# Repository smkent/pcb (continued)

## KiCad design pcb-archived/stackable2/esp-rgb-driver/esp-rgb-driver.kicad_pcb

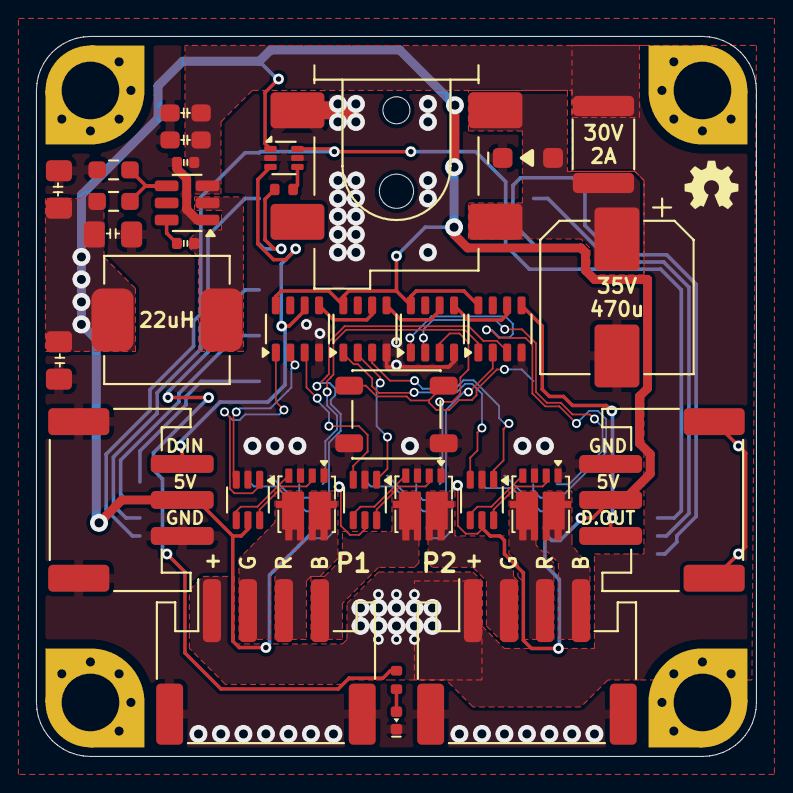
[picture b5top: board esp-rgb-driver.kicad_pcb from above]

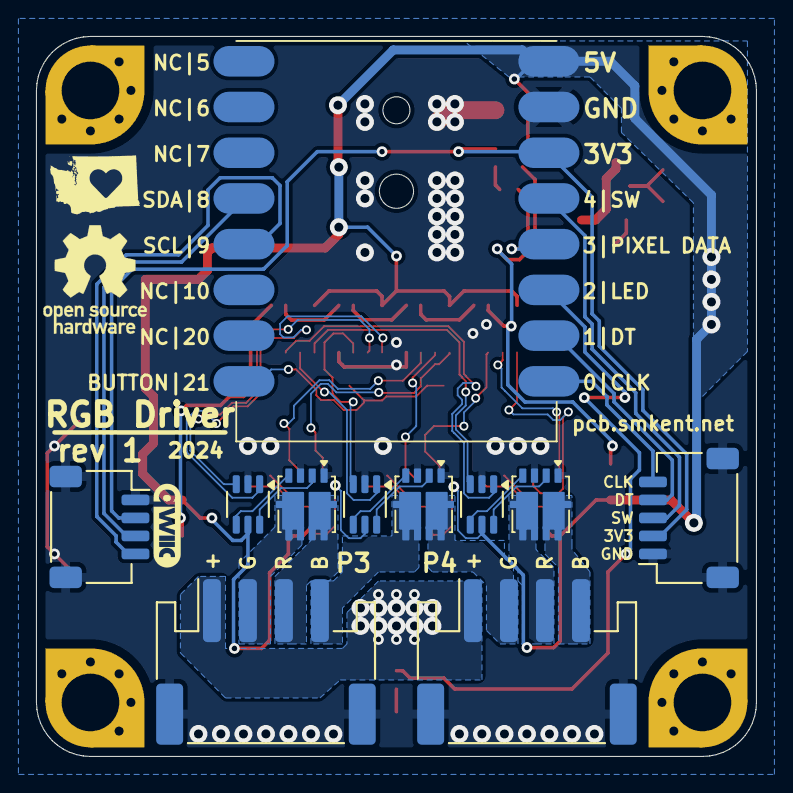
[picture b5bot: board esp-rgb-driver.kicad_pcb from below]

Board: 2 copper layers, 40.0 x 40.0 mm, 45 parts (11 on the bottom side), 59 nets.

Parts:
C0: 470u; CP_Elec_8x10
C1, C2: 10u; C_0603_1608Metric_Pad1.08x0.95mm_HandSolder
C3, C4: 0u1; C_0402_1005Metric
C5, C6, C7: 22u; C_0805_2012Metric_Pad1.18x1.45mm_HandSolder
D1: D_TVS; D_SOD-123F
F1: 30V 2A; Fuse_1812_4532Metric
J0: Barrel Jack; BarrelJack_DC-050_SMT_Horizontal
J1, J2, J3, J4: JST PH; JST_PH_S4B-PH-SM4-TB_1x04-1MP_P2.00mm_Horizontal
J5, J6: STEMMA-Signal; STEMMA-Signal-SMD-horizontal
J7: JST SH; JST_SH_SM05B-SRSS-TB_1x05-1MP_P1.00mm_Horizontal
J8: Qwiic; Qwiic-SMD-horizontal-logo
L1: 22u; L_Power_7.0x6.6mm_0630
LED1: LED; LED_0402_1005Metric
Q1, Q2, Q3, Q4, Q5, Q6: ZC010DNG; PDFN-8_L3.2-W3.1-P0.65-LS3.4-BL-EP2
R1: 100K; R_0603_1608Metric_Pad0.98x0.95mm_HandSolder
R2: 13K3; R_0603_1608Metric_Pad0.98x0.95mm_HandSolder
R3: 300R; R_0402_1005Metric
R4: 10K; R_0402_1005Metric
SM1: ESP32-C3-Super-Mini-Castellated-SMD-only
SW1: SW_Push; SW_SPST_PTS647_Sx50
U1: TPS54202DDCR; SOT-23-6
U2: SN74LVC1T45Z6; SOT-563
U3, U4, U5, U6: WS2811F; FSOP-8_3.3x1.7mm_P0.80mm
U7, U8, U9, U10, U11, U12: NC7WZ14P6X; SOT-363_SC-70-6_HandSolder

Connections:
+3V3: J7.2, J8.2 (+3V3), SM1.3V3 (+3.3V), U2.6 (VCCB)
+5V: C5.1, C6.1, C7.1, J5.2 (V+), J6.2 (V+), L1.2, R1.2, SM1.5V (+5V), U2.1 (VCCA), U3.8 (VDD), U4.8 (VDD), U5.8 (VDD), U6.8 (VDD), U7.5 (V_{CC}), U8.5 (V_{CC}), U9.5 (V_{CC}), U10.5 (V_{CC}), U11.5 (V_{CC}), U12.5 (V_{CC})
+24V: C1.1, C2.1, C3.1, F1.2, J1.1, J2.1, J3.1, J4.1, U1.3 (VIN)
/24V_RAW: C0.1, D1.2 (A2), F1.1, J0.1
/RGB1_B_GATE: Q2.4 (G), U8.4 (2Y)
/RGB1_G_GATE: Q1.4 (G), U7.4 (2Y)
/RGB1_R_GATE: Q1.2 (G), U7.6 (1Y)
/RGB2_B_GATE: Q3.2 (G), U9.6 (1Y)
/RGB2_G_GATE: Q2.2 (G), U8.6 (1Y)
/RGB2_R_GATE: Q3.4 (G), U9.4 (2Y)
/RGB3_B_GATE: Q5.4 (G), U11.4 (2Y)
/RGB3_G_GATE: Q4.4 (G), U10.4 (2Y)
/RGB3_R_GATE: Q4.2 (G), U10.6 (1Y)
/RGB4_B_GATE: Q6.2 (G), U12.6 (1Y)
/RGB4_G_GATE: Q5.2 (G), U11.6 (1Y)
/RGB4_R_GATE: Q6.4 (G), U12.4 (2Y)
/SW: C4.2, L1.1, U1.2 (SW)
BUTTON: SM1.21 (GPIO21/TX), SW1.1
ENCODER_BUTTON: J7.3, SM1.4 (SCK/ADC/GPIO4)
ENCODER_CLK: J7.5, SM1.0 (ADC/GPIO0)
ENCODER_DT: J7.4, SM1.1 (ADC/GPIO1)
FB: R1.1, R2.2, U1.4 (FB)
GND: C0.2, C1.2, C2.2, C3.2, C5.2, C6.2, C7.2, D1.1 (A1), J0.2, J1.MP (MountPin), J2.MP (MountPin), J3.MP (MountPin), J4.MP (MountPin), J5.3 (GND), J5.MP, J6.3 (GND), J6.MP, J7.1, J7.MP (MountPin), J8.1 (GND), J8.MP, LED1.1 (K), Q1.1 (S), Q1.3 (S), Q2.1 (S), Q2.3 (S), Q3.1 (S), Q3.3 (S), Q4.1 (S), Q4.3 (S), Q5.1 (S), Q5.3 (S), Q6.1 (S), Q6.3 (S), R2.1, SM1.G (GND), SW1.2, U1.1 (GND), U2.2 (GND), U2.5 (DIR), U3.4 (GND), U4.4 (GND), U5.4 (GND), U6.4 (GND), U7.2 (GND), U8.2 (GND), U9.2 (GND), U10.2 (GND), U11.2 (GND), U12.2 (GND)
unnamed: LED1.2 (A), R4.2
unnamed: C4.1, U1.6 (BOOT)
unnamed: R3.1, U2.4 (B)
unnamed: U3.5 (DO), U4.6 (DIN)
unnamed: U4.5 (DO), U5.6 (DIN)
unnamed: U5.5 (DO), U6.6 (DIN)
PIXEL_DATA_3V3: R3.2, SM1.3 (ADC/GPIO3)
PIXEL_DATA_5V: J5.1 (Sig), U2.3 (A), U3.6 (DIN)
PIXEL_DATA_OUT: J6.1 (Sig), U6.5 (DO)
RGB1_B: J1.4, Q2.6 (D)
RGB1_B_EN: U3.3 (OUTB), U8.3 (2A)
RGB1_G: J1.2, Q1.6 (D)
RGB1_G_EN: U3.2 (OUTG), U7.3 (2A)
RGB1_R: J1.3, Q1.5 (D)
RGB1_R_EN: U3.1 (OUTR), U7.1 (1A)
RGB2_B: J2.4, Q3.5 (D)
RGB2_B_EN: U4.3 (OUTB), U9.1 (1A)
RGB2_G: J2.2, Q2.5 (D)
RGB2_G_EN: U4.2 (OUTG), U8.1 (1A)
RGB2_R: J2.3, Q3.6 (D)
RGB2_R_EN: U4.1 (OUTR), U9.3 (2A)
RGB3_B: J3.4, Q5.6 (D)
RGB3_B_EN: U5.3 (OUTB), U11.3 (2A)
RGB3_G: J3.2, Q4.6 (D)
RGB3_G_EN: U5.2 (OUTG), U10.3 (2A)
RGB3_R: J3.3, Q4.5 (D)
RGB3_R_EN: U5.1 (OUTR), U10.1 (1A)
RGB4_B: J4.4, Q6.5 (D)
RGB4_B_EN: U6.3 (OUTB), U12.1 (1A)
RGB4_G: J4.2, Q5.5 (D)
RGB4_G_EN: U6.2 (OUTG), U11.1 (1A)
RGB4_R: J4.3, Q6.6 (D)
RGB4_R_EN: U6.1 (OUTR), U12.3 (2A)
SCL: J8.4 (SCL), SM1.9 (~GPIO9/SCL)
SDA: J8.3 (SDA), SM1.8 (~GPIO8/SDA)
STATUS_LED: R4.1, SM1.2 (ADC/~GPIO2)

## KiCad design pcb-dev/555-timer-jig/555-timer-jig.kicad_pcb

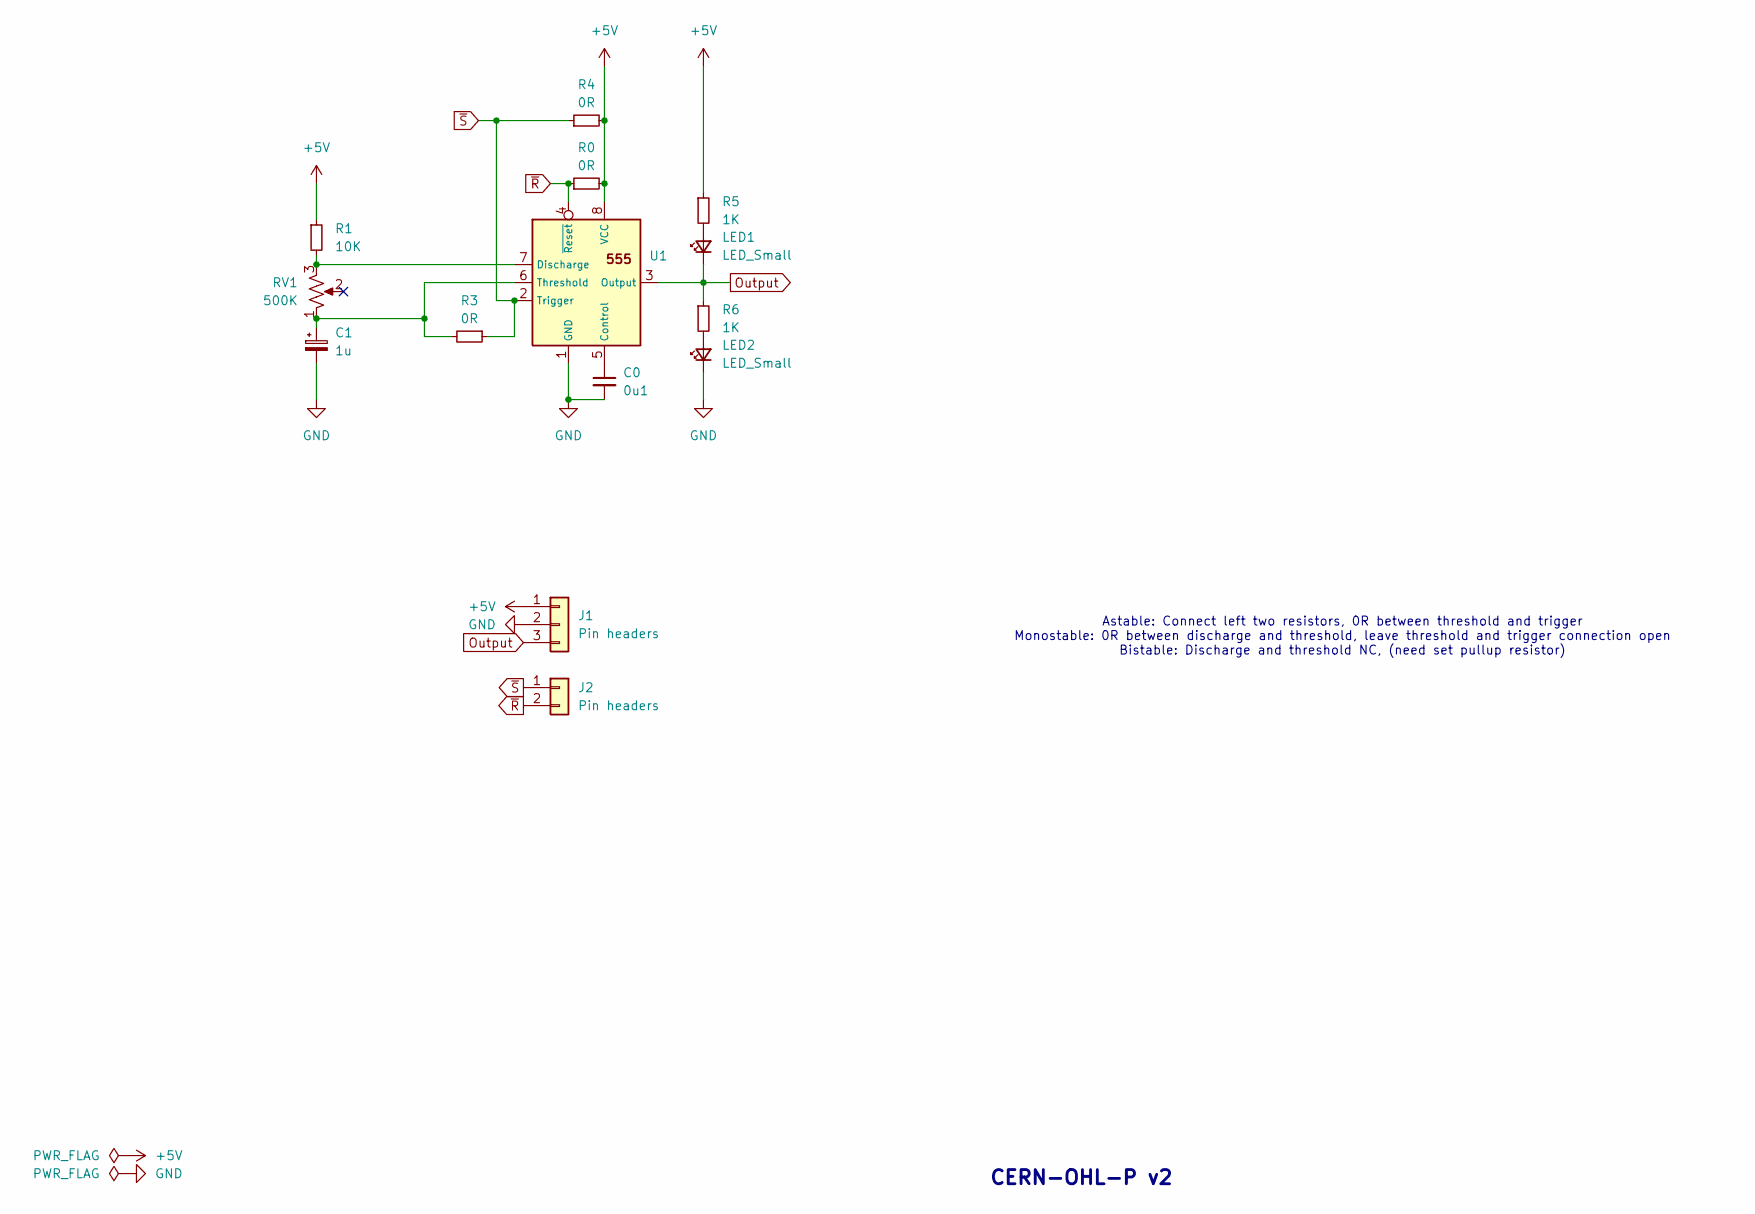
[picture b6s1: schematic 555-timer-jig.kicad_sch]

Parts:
C0: 0u1; C_0603_1608Metric_Pad1.08x0.95mm_HandSolder
C1: 1u; C_Combo_CP_Elec_5x5.4
J1: Pin headers; PinHeader_1x03_P2.54mm_Vertical_simple_pad2gnd
J2: Pin headers; PinHeader_1x02_P2.54mm_Vertical_simple
LED1, LED2: LED_Small; LED_0603_1608Metric_Pad1.05x0.95mm_HandSolder_simple
R0, R3, R4: 0R; R_0603_1608Metric_Pad0.98x0.95mm_HandSolder_simple
R1: 10K; R_0603_1608Metric_Pad0.98x0.95mm_HandSolder_simple
R5, R6: 1K; R_0603_1608Metric_Pad0.98x0.95mm_HandSolder_simple
RV1: 500K; RES-ADJ-SMD_VG039NCH
U1: NE555; SOIC-8_3.9x4.9mm_P1.27mm

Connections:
+5V: J1.1, R0.2, R1.1, R4.2, R5.1, U1.8 (VCC)
GND: C0.2, C1.2, J1.2, LED2.1 (K), U1.1 (GND)
unnamed: LED1.2 (A), R5.2
unnamed: LED2.2 (A), R6.2
unnamed: C0.1, U1.5 (Control)
unnamed: R1.2, RV1.3, U1.7 (Discharge)
unnamed: C1.1, R3.2, RV1.1, U1.6 (Threshold)
Output: J1.3, LED1.1 (K), R6.1, U1.3 (Output)
~R: J2.2, R0.1, U1.4 (~Reset)
~S: J2.1, R3.1, R4.1, U1.2 (Trigger)

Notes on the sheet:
CERN-OHL-P v2
Astable: Connect left two resistors, 0R between threshold and trigger Monostable: 0R between discharge and threshold, leave threshold and trigger connection open Bistable: Discharge and threshold NC, (need set pullup resistor)

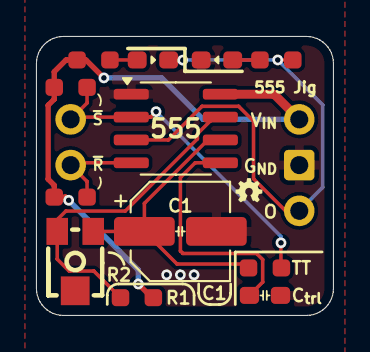
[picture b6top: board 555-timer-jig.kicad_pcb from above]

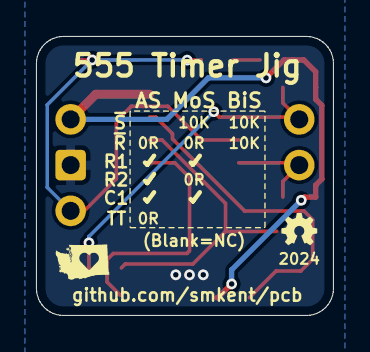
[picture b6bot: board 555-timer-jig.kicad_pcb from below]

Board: 2 copper layers, 16.5 x 15.5 mm, 14 parts (2 on the bottom side), 10 nets.

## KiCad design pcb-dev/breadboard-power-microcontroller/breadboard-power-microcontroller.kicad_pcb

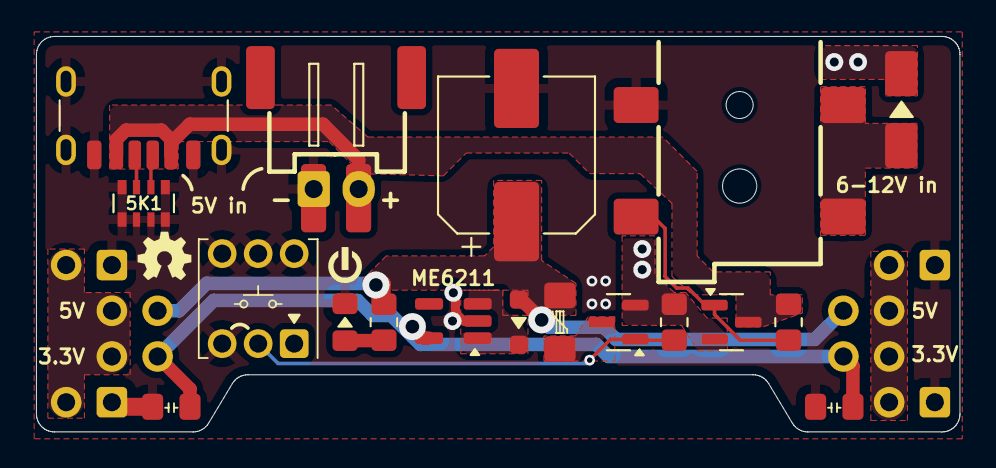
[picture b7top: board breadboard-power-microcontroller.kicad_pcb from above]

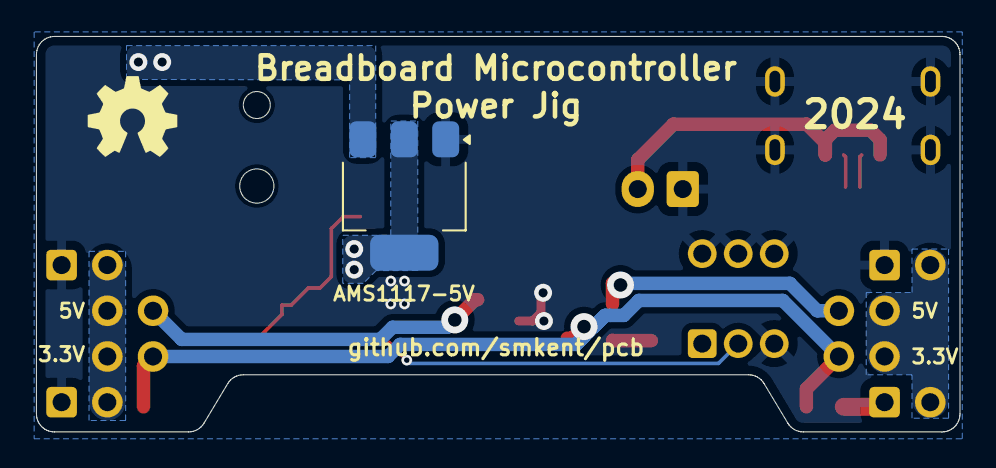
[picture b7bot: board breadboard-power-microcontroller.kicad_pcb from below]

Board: 2 copper layers, 51.3 x 22.0 mm, 25 parts (5 on the bottom side), 16 nets.

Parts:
C1: 1000uF; CP_Elec_8x10.5
C2, C3: 22uF; C_0805_2012Metric_Pad1.18x1.45mm_HandSolder
D1: SS34; D_SMA_simple
D2: BAT60A; D_SOD-323_HandSoldering_simple
D3: LED; LED_0805_2012Metric_Pad1.15x1.40mm_HandSolder_simple
F1: Polyfuse; Fuse_1206_3216Metric_Pad1.42x1.75mm_HandSolder_simple
J0: USB_C_Receptacle_PowerOnly_6P; USB_C_Receptacle_GCT_USB4125-xx-x_6P_TopMnt_Horizontal_hand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
J1: Barrel_Jack_Switch; DC-IN_DC-050-2.0-BB_rev2
J2: Conn_01x02; JST_XH_S2B-XH-2AW_1x02_P2.50mm_TH-or-SMD_pad2gnd_trim
JLEFT0, JLEFT1: Conn_01x02; PinHeader_1x02_P2.54mm_Vertical_simple_pad2gnd
JLEFT2: Conn_02x02_Counter_Clockwise; PinHeader_2x02_P2.54mm_Vertical_simple
JRIGHT0, JRIGHT1: Conn_01x02; PinHeader_1x02_P2.54mm_Vertical_simple_pad2gnd
JRIGHT2: Conn_02x02_Counter_Clockwise; PinHeader_2x02_P2.54mm_Vertical_simple
Q1, Q2: AO3401A; SOT-23
R1, R2: 10K; R_0805_2012Metric_Pad1.20x1.40mm_HandSolder
R6: 2K2; R_0805_2012Metric_Pad1.20x1.40mm_HandSolder
RN1: 5K1; R_Array_Convex_4x0603
SW1: SW_DPDT_x2; SW-TH_6P-L7.0-W7.0-P2.00_90deg
U1: AMS1117-5.0; SOT-223-3_TabPin2
U2: ME6211C33M5; SOT-23-5_HandSoldering_simple

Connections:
3V3_OUT: C2.1, C3.1, JLEFT2.4, JRIGHT2.3, U2.5 (V_{OUT})
5V_OUT: C1.1, D2.2 (A), F1.2, JLEFT2.2, JRIGHT2.1, R6.1
DC_IN_DIODE: D1.1 (K), U1.3 (VI)
DC_JACK_SWITCH: J1.3, Q2.1 (G), R1.1
GND: C1.2, C2.2, C3.2, D3.1 (K), J0.A12 (GND), J0.B12 (GND), J0.S1 (SHIELD), J1.2, J2.2, JLEFT0.2, JLEFT1.2, JRIGHT0.2, JRIGHT1.2, RN1.1 (R1.1), RN1.4 (R4.1), RN1.5 (R4.2), RN1.6 (R3.2), RN1.7 (R2.2), RN1.8 (R1.2), SW1.3 (C), SW1.4 (A), SW1.5 (B), SW1.6 (C), U1.1 (GND), U2.2 (V_{SS})
unnamed: D3.2 (A), R6.2
unnamed: J0.A5 (CC1), RN1.2 (R2.1)
unnamed: J0.B5 (CC2), RN1.3 (R3.1)
unnamed: Q1.1 (G), R2.2, SW1.2 (B)
PRE_FUSE: F1.1, Q1.3 (D)
REG_5V: Q1.2 (S), Q2.2 (S), R2.1, U1.2 (VO)
TO_3V3_DIODE: D2.1 (K), U2.1 (V_{IN}), U2.3 (CE)
VIN: J0.A9 (VBUS), J0.B9 (VBUS), J2.1, Q2.3 (D), R1.2
VIN_DC: D1.2 (A), J1.1
VOUT_LEFT: JLEFT0.1, JLEFT1.1, JLEFT2.1, JLEFT2.3
VOUT_RIGHT: JRIGHT0.1, JRIGHT1.1, JRIGHT2.2, JRIGHT2.4

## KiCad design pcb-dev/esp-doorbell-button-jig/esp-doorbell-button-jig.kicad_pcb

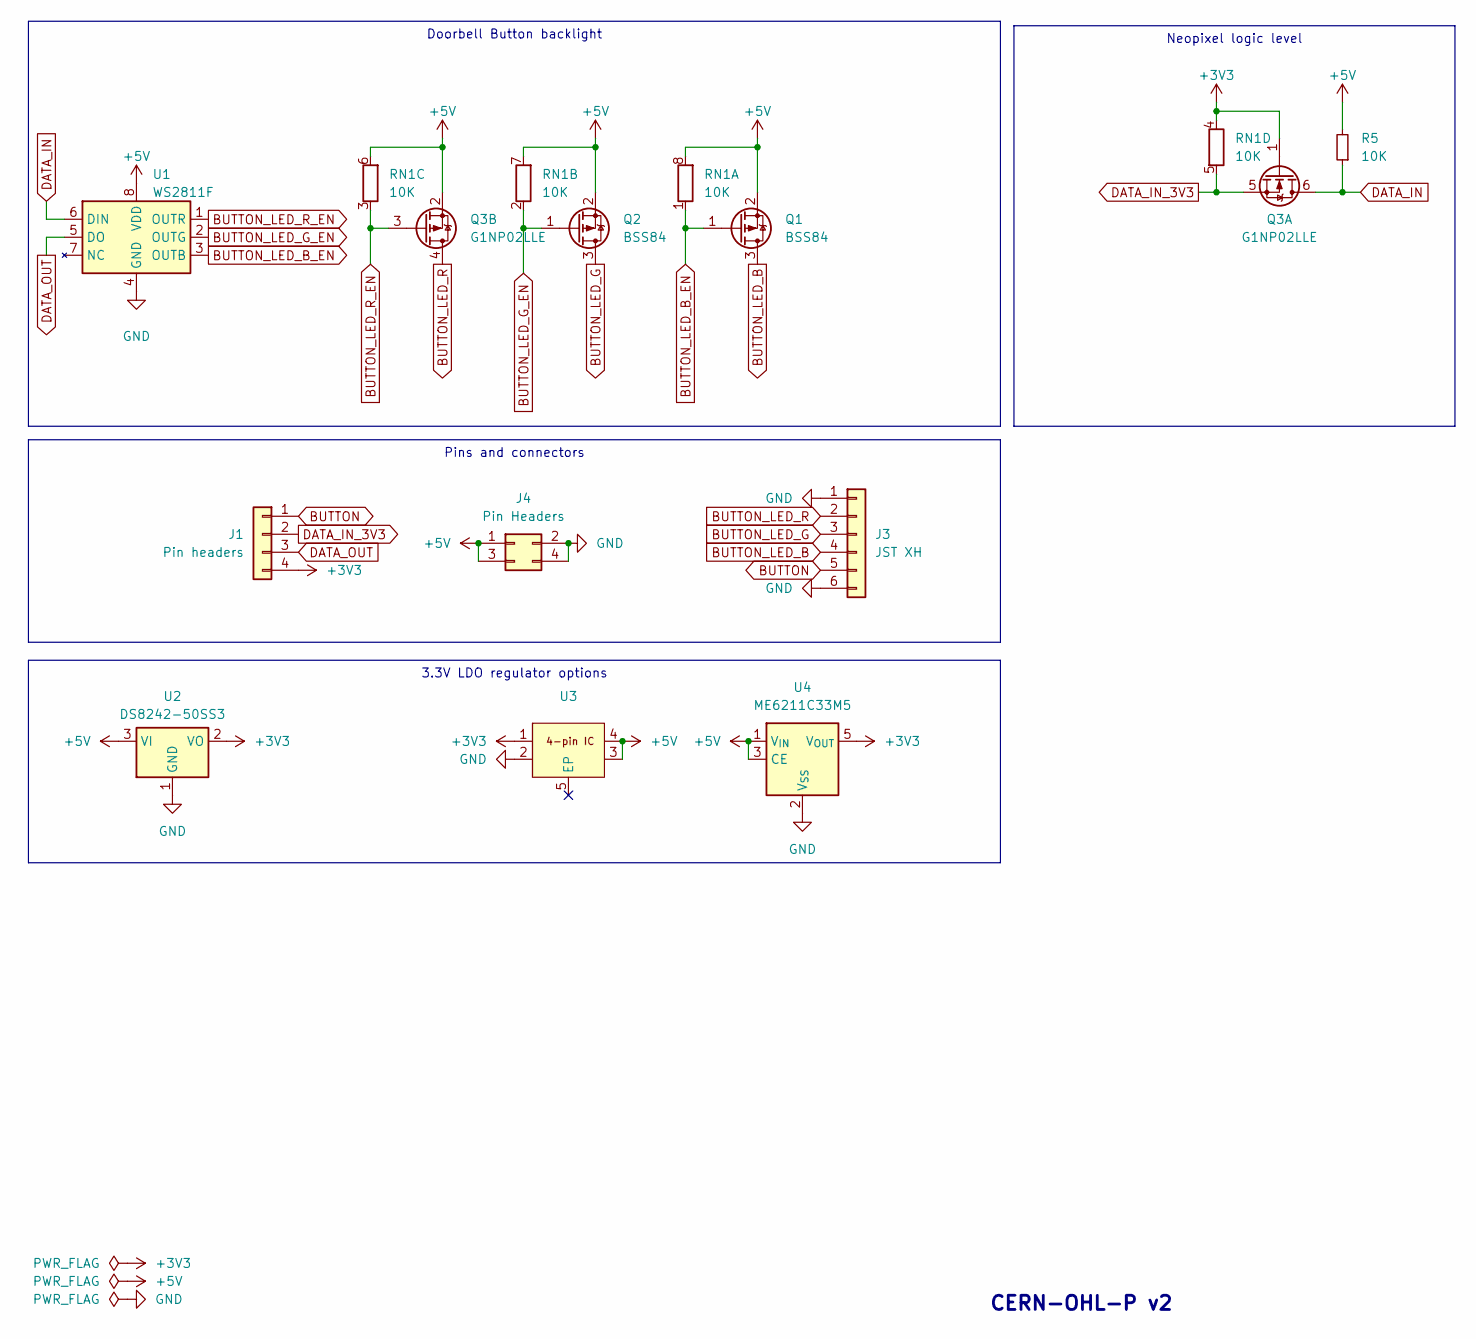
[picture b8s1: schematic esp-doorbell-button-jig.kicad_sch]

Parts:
J1: Pin headers; PinHeader_1x04_P2.54mm_Vertical_simple
J3: JST XH; JST_XH_B6B-XH-A_1x06_P2.50mm_Vertical_slim
J4: Pin Headers; PinHeader_2x02_P2.54mm_Vertical_simple
Q1, Q2: BSS84; SOT-23_simple
Q3: G1NP02LLE; SOT-23-6_simple; LCSC Part C7465318
R5: 10K; R_0603_1608Metric
RN1: 10K; R_Array_Convex_4x0603
U1: WS2811F; FSOP-8_L3.3-W1.7-P0.80-LS2.9-BL; LCSC Part C5446692
U2: DS8242-50SS3; SOT-23_simple; LCSC Part C5884141
U3: Texas_X2SON-4_1x1mm_P0.65mm
U4: ME6211C33M5; SOT-23-5_simple

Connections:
+3V3: J1.4, Q3.1 (G), RN1.4 (R4.1), U2.2 (VO), U3.1, U4.5 (V_{OUT})
+5V: J4.1, J4.3, Q1.2 (S), Q2.2 (S), Q3.2 (S), R5.2, RN1.6 (R3.2), RN1.7 (R2.2), RN1.8 (R1.2), U1.8 (VDD), U2.3 (VI), U3.3, U3.4, U4.1 (V_{IN}), U4.3 (CE)
BUTTON: J1.1, J3.5
BUTTON_LED_B: J3.4, Q1.3 (D)
BUTTON_LED_B_EN: Q1.1 (G), RN1.1 (R1.1), U1.3 (OUTB)
BUTTON_LED_G: J3.3, Q2.3 (D)
BUTTON_LED_G_EN: Q2.1 (G), RN1.2 (R2.1), U1.2 (OUTG)
BUTTON_LED_R: J3.2, Q3.4 (D)
BUTTON_LED_R_EN: Q3.3 (G), RN1.3 (R3.1), U1.1 (OUTR)
DATA_IN: Q3.6 (D), R5.1, U1.6 (DIN)
DATA_IN_3V3: J1.2, Q3.5 (S), RN1.5 (R4.2)
DATA_OUT: J1.3, U1.5 (DO)
GND: J3.1, J3.6, J4.2, J4.4, U1.4 (GND), U2.1 (GND), U3.2, U4.2 (V_{SS})

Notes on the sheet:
Neopixel logic level
3.3V LDO regulator options
Pins and connectors
Doorbell Button backlight
CERN-OHL-P v2

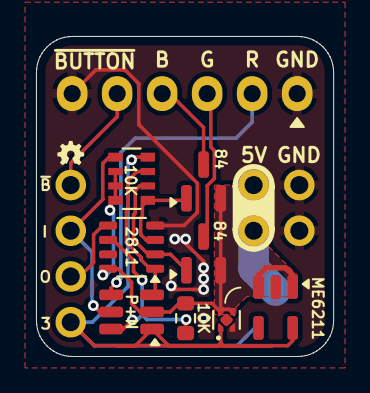
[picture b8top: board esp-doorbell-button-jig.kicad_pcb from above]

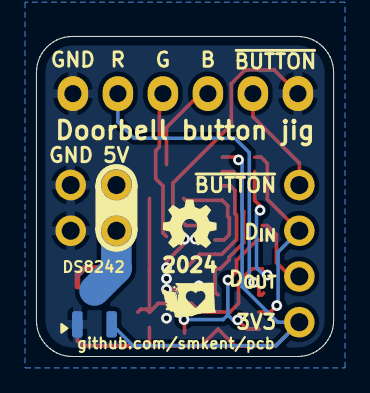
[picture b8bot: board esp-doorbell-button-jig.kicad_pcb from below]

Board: 2 copper layers, 16.5 x 17.8 mm, 12 parts (3 on the bottom side), 13 nets.
